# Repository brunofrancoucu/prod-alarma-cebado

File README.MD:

# Consigna
A nivel mundial, cerca de 100 millones de personas sufren de
deshidratación anualmente. Eso equivale a 3 personas por segundo!
Es nuestro deber recordar a la gente a mantenerse hidratada!

Objetivo: Hacer una alarma para tomar mate. Deben diseñar el esquemático y PCB (en KiCad), partiendo del circuito
dispuesto, y generar una bill of materials (BOM) completa.
# kicad - Esquematico y layout

Proceso de diseno placa conexiones electricas entre componentes, alineado de componentes, soldadura y manejo en gral, medición de señales, eventuales hotfixes. 
[consideraciones](/board/README.MD), [calculos](/board/README.MD#calculos), [BOM](/BOM.html)
# Autodesk Inventor - Encapsulado

Proceso de diseno del envolvente plastico
[consideraciones](/enclosure/README.md#consideraciones-housingipt)

# Producto Final

Feedback:
- Contra-peso [return force](https://www.digikey.com/en/products/detail/same-sky-formerly-cui-devices/TS02-66-90-BK-260-SCR-D/15634305) (btn push)
- USB-c
- Bateria (Conexion a placa)

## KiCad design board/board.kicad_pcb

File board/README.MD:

# Ruteo de alta frecuencia con coupling a GND Y PWR
Par diferencial de alta frecuencia por multiples capas, respetando la impedancia el return path sera por PWR (debido a stack up intermedio de GND PWR y no GND GND), por ello utilizar capacitor en puntos de entrada (source) y salida (exit) (split boundary)

### Stitching capacitor:
[ref1](https://www.asset-intertech.com/wp-content/uploads/2020/05/6a01348365b3a6970c01b8d06c22f7970c-pi.jpg), [ref2](https://www.protoexpress.com/blog/wp-content/uploads/2020/05/28.png)
Valores normales para el stitching capacitor ronda los, 10nF and 100nF [src](https://www.protoexpress.com/blog/best-high-speed-pcb-routing-practices/)
Evitar: "If that plane is cut, the return current must detour—often radiating or coupling into other nets—and you’ll get reflections, EMI, and extra crosstalk" - gpt

# Calculos:
### Par diferencial:

Z0: 90ohms +-15%
w: εᵣ 4.6 7628 prepreg FR-4 glass-epoxy laminate [ref](https://jlcpcb.com/capabilities/pcb-capabilities)
h: 0.2mm
Ancho pista: 0.202 mm - separacion pista recomendada: 0.062 mm, maxima: 0.329 mm

### Stitching capacitor, "capacitancia ideal":
Frequencia usb 3.0: 2.5 Ghz (medible con el "rise time" de la señal), entonces, para un Zdiff de 90 ohmios el Zbridge resulta 9 ohmios, capacitancia minima: 7.1 pF
- 100 nF 0402 or 0201	for low-frequency return (10 kHz – 100 MHz)	
- 1 nF 0201	covers 100 MHz – 1 GHz
- 100 pF 0201	covers 1 GHz – 3.5+ GHz (✔️ Recomendable)

Nos aseguramos: effective throughput (bit errors), calidad de señal compliance al USB.

# Complemento

### Recomendacion (plano de referencia limpio): SIG, GND, GND, (SIG + PWR)
Objetivo / desafio: mantener bajo cross talk con un coupling corto / cercano (usando PWR como plano de referencia)

### Otras alternativas:
- GND temporal en PWR (capa 3), justo arriba de par diferencial en la 4ta capa (SIG).
- Rutearlo por arriba.

# TODO
- Bateria Litio recargable
- Entrada USB-C
- Comunicacion puerto UART (notificacion escritorio)

## Gerbers
`File > Export > Fabrication Outputs > Gerbers`
1. `Generate Drill Files...` Gerber X2
2. RUN DRC...
3. Plot
4. Verificar en `Gerber View`

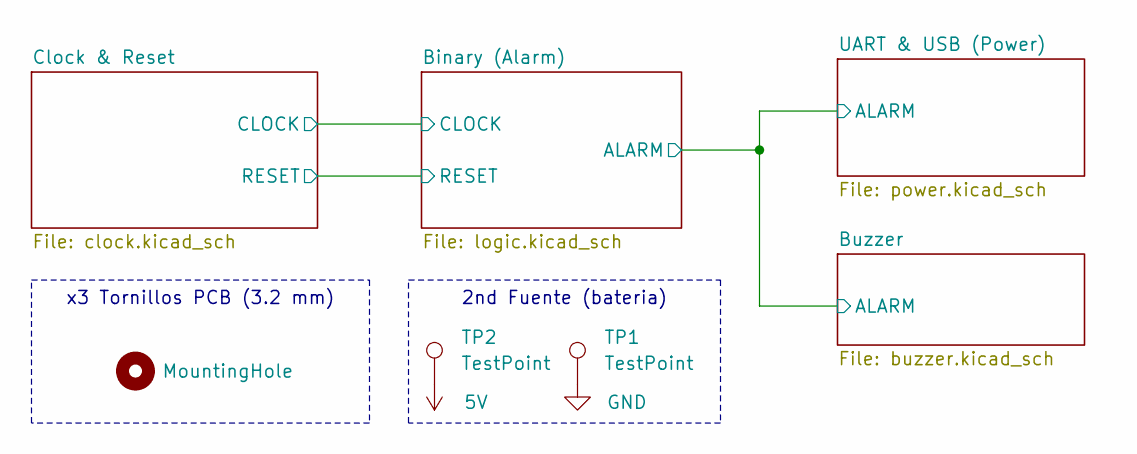
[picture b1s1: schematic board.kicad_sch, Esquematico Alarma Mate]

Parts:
H1: MountingHole; MountingHole_3.2mm_M3
TP1: TestPoint; TestPoint_THTPad_2.0x2.0mm_Drill1.0mm
TP2: TestPoint; TestPoint_THTPad_D2.0mm_Drill1.0mm

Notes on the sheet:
2nd Fuente (bateria)
x3 Tornillos PCB (3.2 mm)

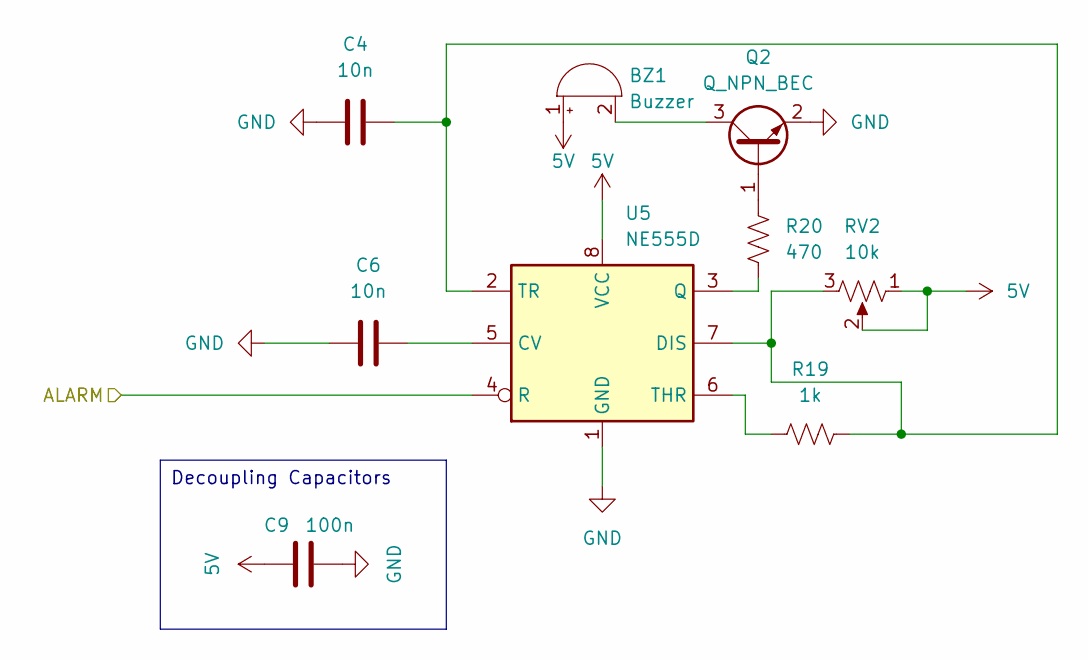
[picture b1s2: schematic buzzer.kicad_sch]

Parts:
BZ1: Buzzer; MagneticBuzzer_PUI_AT-0927-TT-6-R
C4, C6: 10n; C_0603_1608Metric
C9: 100n; C_0603_1608Metric
Q2: Q_NPN_BEC; SOT-23
R19: 1k; R_0603_1608Metric
R20: 470; R_0603_1608Metric
RV2: 10k; Potentiometer_Piher_PT-6-V_Vertical
U5: NE555D; SOIC-8_3.9x4.9mm_P1.27mm

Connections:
5V: BZ1.1 (+), C9.1, RV2.1, RV2.2, U5.8 (VCC); also elsewhere on the board
ALARM: U5.4 (R); also elsewhere on the board
GND: C4.2, C6.1, C9.2, Q2.2 (E), U5.1 (GND); also elsewhere on the board
unnamed: BZ1.2 (-), Q2.3 (C)
unnamed: Q2.1 (B), R20.1
unnamed: C6.2, U5.5 (CV)
unnamed: C4.1, R19.1, RV2.3, U5.2 (TR), U5.7 (DIS)
unnamed: R20.2, U5.3 (Q)
unnamed: R19.2, U5.6 (THR)

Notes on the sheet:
Decoupling Capacitors

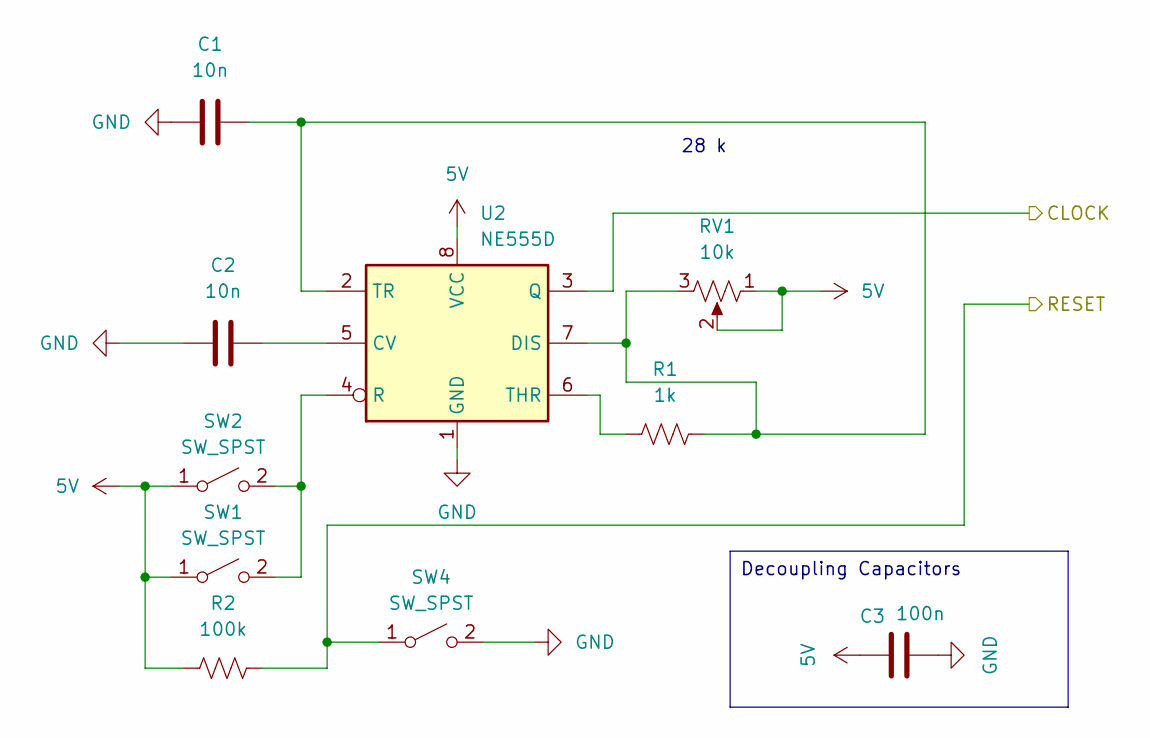
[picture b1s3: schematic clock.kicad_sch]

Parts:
C1, C2: 10n; C_0603_1608Metric
C3: 100n; C_0603_1608Metric
R1: 1k; R_0603_1608Metric
R2: 100k; R_0603_1608Metric
RV1: 10k; Potentiometer_Piher_PT-6-V_Vertical
SW1, SW2, SW4: SW_SPST; SW_PUSH_6mm_H4.3mm
U2: NE555D; SOIC-8_3.9x4.9mm_P1.27mm

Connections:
5V: C3.1, R2.1, RV1.1, RV1.2, SW1.1 (A), SW2.1 (A), U2.8 (VCC); also elsewhere on the board
CLOCK: U2.3 (Q); also elsewhere on the board
GND: C1.2, C2.1, C3.2, SW4.2 (B), U2.1 (GND); also elsewhere on the board
unnamed: SW1.2 (B), SW2.2 (B), U2.4 (R)
unnamed: C2.2, U2.5 (CV)
unnamed: C1.1, R1.1, RV1.3, U2.2 (TR), U2.7 (DIS)
unnamed: R1.2, U2.6 (THR)
RESET: R2.2, SW4.1 (A); also elsewhere on the board

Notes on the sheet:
28 k
Decoupling Capacitors

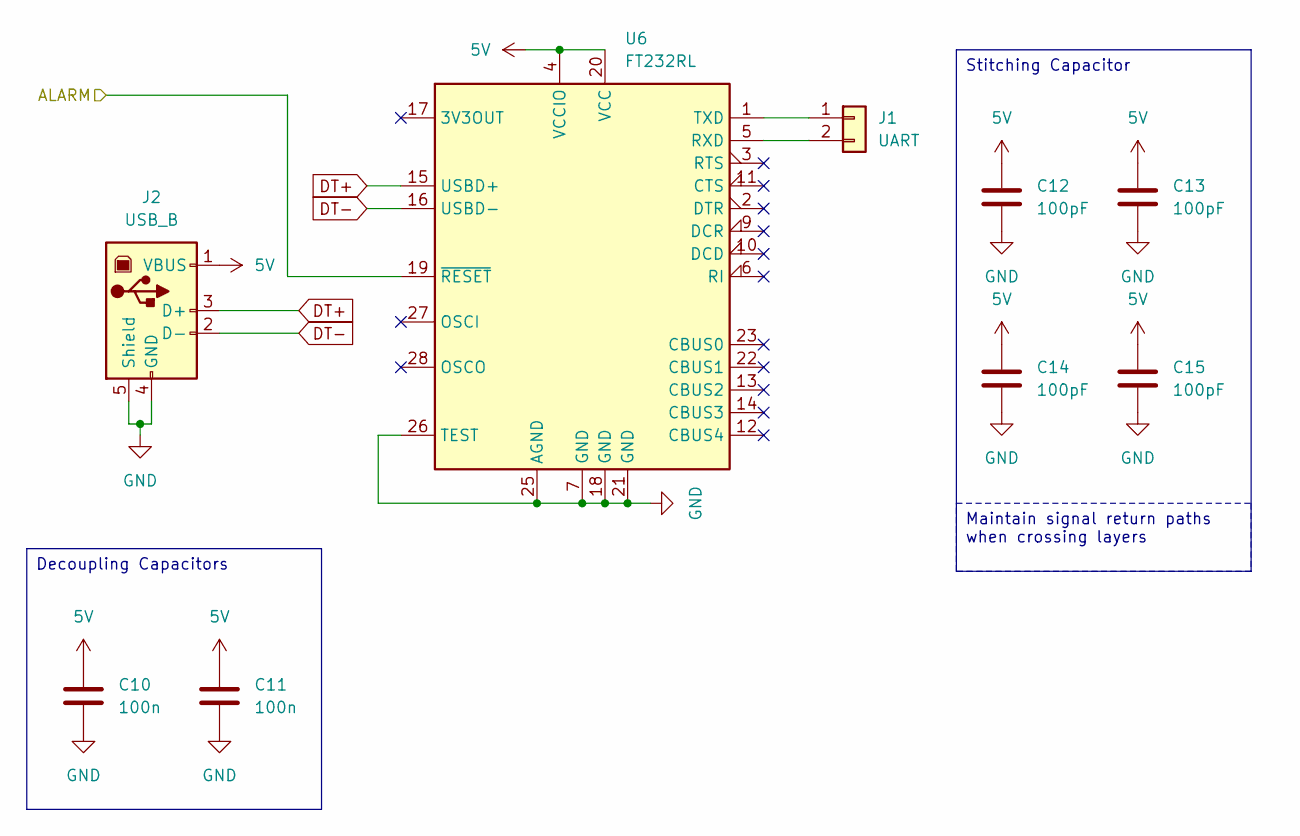
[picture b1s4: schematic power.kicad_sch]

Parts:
C10, C11: 100n; C_0603_1608Metric
C12, C13, C14, C15: 100pF; C_0201_0603Metric
J1: UART; PinSocket_1x02_P2.54mm_Vertical
J2: USB_B; USB_Mini-B_Lumberg_2486_01_Horizontal
U6: FT232RL; SSOP-28_5.3x10.2mm_P0.65mm

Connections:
5V: C10.1, C11.1, C12.1, C13.1, C14.1, C15.1, J2.1 (VBUS), U6.4 (VCCIO), U6.20 (VCC); also elsewhere on the board
ALARM: U6.19 (~RESET); also elsewhere on the board
DT+: J2.3 (D+), U6.15 (USBD+)
DT-: J2.2 (D-), U6.16 (USBD-)
GND: C10.2, C11.2, C12.2, C13.2, C14.2, C15.2, J2.4 (GND), J2.5 (Shield), U6.7 (GND), U6.18 (GND), U6.21 (GND), U6.25 (AGND), U6.26 (TEST); also elsewhere on the board
unnamed: J1.1, U6.1 (TXD)
unnamed: J1.2, U6.5 (RXD)

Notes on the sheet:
Stitching Capacitor
Maintain signal return paths when crossing layers
Decoupling Capacitors

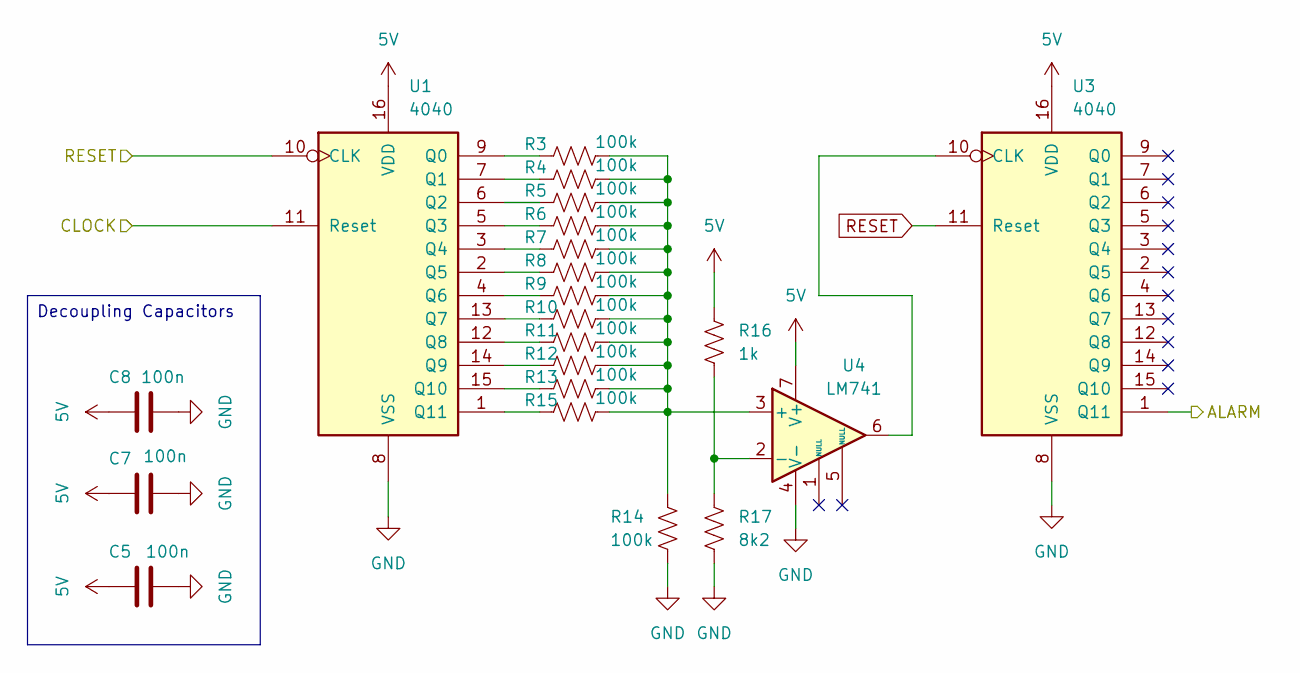
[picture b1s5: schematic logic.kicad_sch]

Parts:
C5, C7, C8: 100n; C_0603_1608Metric
R3, R4, R5, R6, R7, R8, R9, R10, R11, R12, R13, R14, R15: 100k; R_0603_1608Metric
R16: 1k; R_0603_1608Metric
R17: 8k2; R_0603_1608Metric
U1, U3: 4040; SO-16_3.9x9.9mm_P1.27mm
U4: LM741; SOIC-8_3.9x4.9mm_P1.27mm

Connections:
5V: C5.1, C7.1, C8.1, R16.2, U1.16 (VDD), U3.16 (VDD), U4.7 (V+); also elsewhere on the board
ALARM: U3.1 (Q11); also elsewhere on the board
CLOCK: U1.10 (CLK); also elsewhere on the board
GND: C5.2, C7.2, C8.2, R14.1, R17.1, U1.8 (VSS), U3.8 (VSS), U4.4 (V-); also elsewhere on the board
unnamed: R3.1, U1.9 (Q0)
unnamed: R4.1, U1.7 (Q1)
unnamed: R5.1, U1.6 (Q2)
unnamed: R6.1, U1.5 (Q3)
unnamed: R7.1, U1.3 (Q4)
unnamed: R8.1, U1.2 (Q5)
unnamed: R9.1, U1.4 (Q6)
unnamed: R10.1, U1.13 (Q7)
unnamed: R11.1, U1.12 (Q8)
unnamed: R12.1, U1.14 (Q9)
unnamed: R13.1, U1.15 (Q10)
unnamed: R15.1, U1.1 (Q11)
unnamed: U3.10 (CLK), U4.6
unnamed: R3.2, R4.2, R5.2, R6.2, R7.2, R8.2, R9.2, R10.2, R11.2, R12.2, R13.2, R14.2, R15.2, U4.3 (+)
unnamed: R16.1, R17.2, U4.2 (-)
RESET: U1.11 (Reset), U3.11 (Reset); also elsewhere on the board

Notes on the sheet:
Decoupling Capacitors

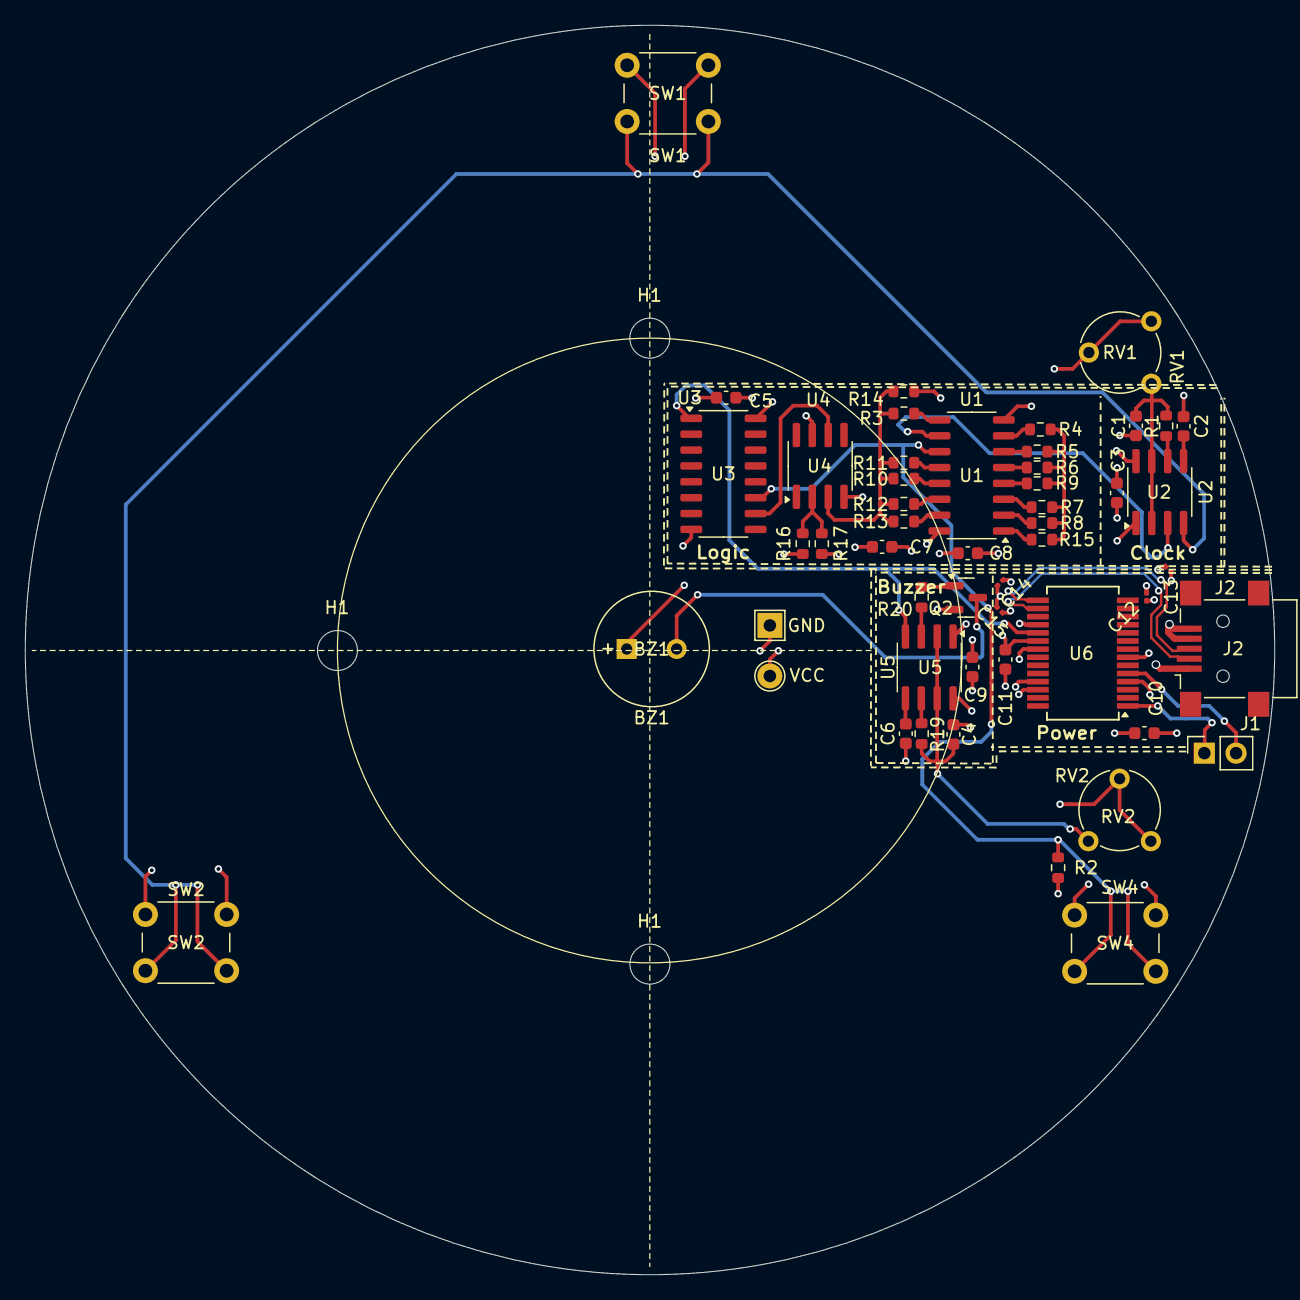
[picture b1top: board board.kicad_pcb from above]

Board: 4 copper layers, 100.0 x 100.0 mm, 54 parts (0 on the bottom side), 34 nets.

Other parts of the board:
GND: TestPoint; TestPoint_THTPad_2.0x2.0mm_Drill1.0mm
H1#2, H1#3: MountingHole; MountingHole_3.2mm_M3
VCC: TestPoint; TestPoint_THTPad_D2.0mm_Drill1.0mm

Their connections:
5V: VCC.1; also elsewhere on the board
GND: GND.1; also elsewhere on the board

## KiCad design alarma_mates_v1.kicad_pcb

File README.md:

# alarma-mates-pcb
Esquemático y diseño de PCB en KiCad de una alarma para tomar mates cada 5 minutos.

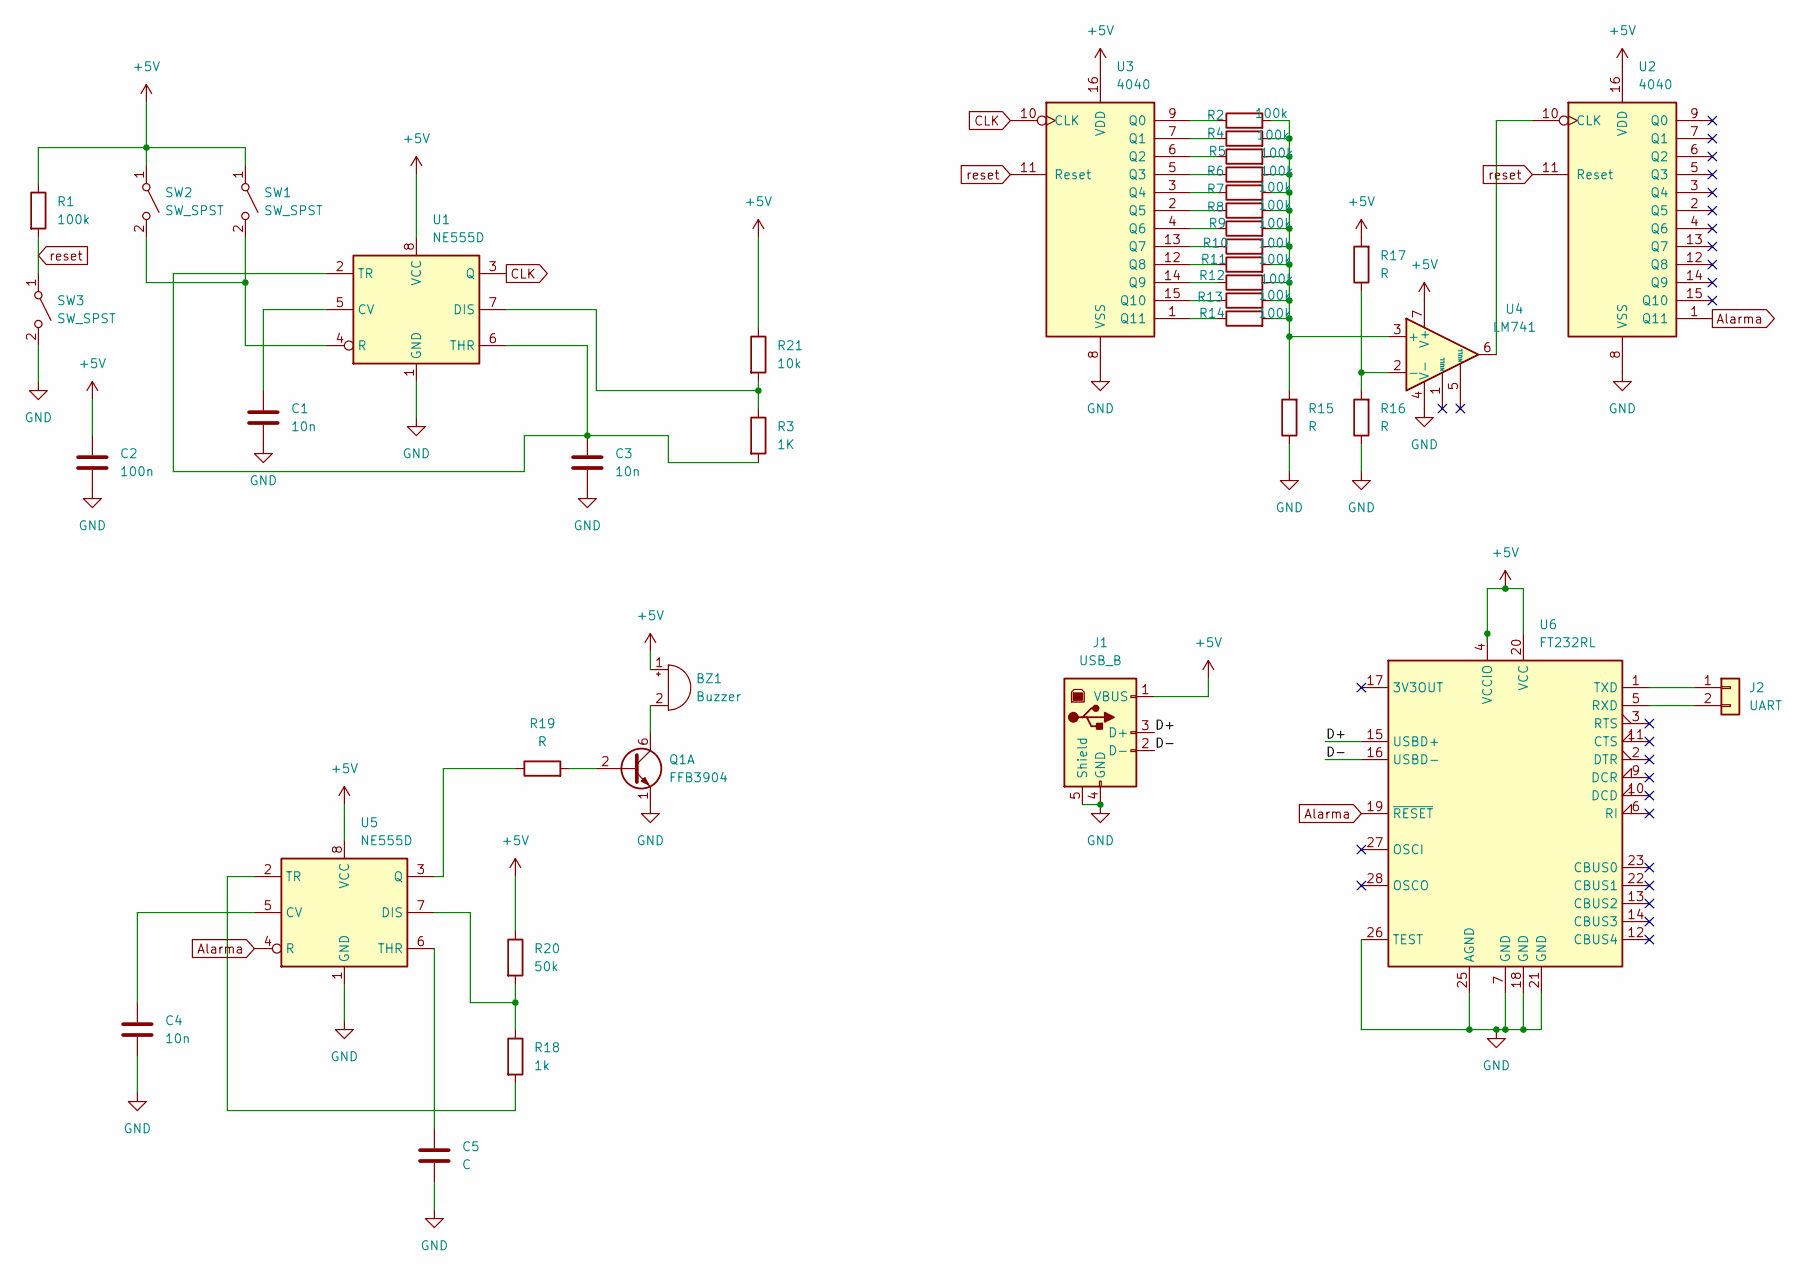
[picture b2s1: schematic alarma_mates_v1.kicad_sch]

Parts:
BZ1: Buzzer; TO_0601A_SOB
C1, C3, C4: 10n; C_0603_1608Metric
C2: 100n; C_0603_1608Metric
C5: C; C_0603_1608Metric
J1: USB_B; CUI_UJ2-MBH-1-SMT
J2: UART; PinHeader_1x02_P1.00mm_Vertical_SMD_Pin1Left
Q1: FFB3904; SOT-23_MCC
R1, R2, R4, R5, R6, R7, R8, R9, R10, R11, R12, R13, R14: 100k; R_0603_1608Metric
R3: 1K; R_0603_1608Metric
R15, R16, R17, R19: R; R_0603_1608Metric
R18: 1k; R_0603_1608Metric
R20: 50k; R_0603_1608Metric
R21: 10k; R_0603_1608Metric
SW1, SW2, SW3: SW_SPST; SW_TS02-66-90-BK-260-SCR-D
U1, U5: NE555D; D8
U2, U3: 4040; SOT109-1_NXP
U4: LM741; D8
U6: FT232RL; SSOP-28_FTD

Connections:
+5V: BZ1.1 (+), C2.1, J1.1 (VBUS), R1.1, R17.2, R20.1, R21.1, SW1.1 (A), SW2.1 (A), U1.8 (VCC), U2.16 (VDD), U3.16 (VDD), U4.7 (V+), U5.8 (VCC), U6.4 (VCCIO), U6.20 (VCC)
/D+: J1.3 (D+), U6.15 (USBD+)
/D-: J1.2 (D-), U6.16 (USBD-)
Alarma: U2.1 (Q11), U5.4 (R), U6.19 (~RESET)
CLK: U1.3 (Q), U3.10 (CLK)
GND: C1.2, C2.2, C3.2, C4.2, C5.2, J1.4 (GND), J1.5 (Shield), Q1.1 (E1), R15.1, R16.1, SW3.2 (B), U1.1 (GND), U2.8 (VSS), U3.8 (VSS), U4.4 (V-), U5.1 (GND), U6.7 (GND), U6.18 (GND), U6.21 (GND), U6.25 (AGND), U6.26 (TEST)
unnamed: BZ1.2 (-), Q1.6 (C1)
unnamed: J2.1, U6.1 (TXD)
unnamed: J2.2, U6.5 (RXD)
unnamed: Q1.2 (B1), R19.2
unnamed: SW1.2 (B), SW2.2 (B), U1.4 (R)
unnamed: C1.1, U1.5 (CV)
unnamed: R3.1, R21.2, U1.7 (DIS)
unnamed: C3.1, R3.2, U1.2 (TR), U1.6 (THR)
unnamed: U2.10 (CLK), U4.6
unnamed: R2.1, U3.9 (Q0)
unnamed: R4.1, U3.7 (Q1)
unnamed: R5.1, U3.6 (Q2)
unnamed: R6.1, U3.5 (Q3)
unnamed: R7.1, U3.3 (Q4)
unnamed: R8.1, U3.2 (Q5)
unnamed: R9.1, U3.4 (Q6)
unnamed: R10.1, U3.13 (Q7)
unnamed: R11.1, U3.12 (Q8)
unnamed: R12.1, U3.14 (Q9)
unnamed: R13.1, U3.15 (Q10)
unnamed: R14.1, U3.1 (Q11)
unnamed: R2.2, R4.2, R5.2, R6.2, R7.2, R8.2, R9.2, R10.2, R11.2, R12.2, R13.2, R14.2, R15.2, U4.3 (+)
unnamed: R16.2, R17.1, U4.2 (-)
unnamed: C4.1, U5.5 (CV)
unnamed: R18.1, R20.2, U5.7 (DIS)
unnamed: R19.1, U5.3 (Q)
unnamed: C5.1, U5.6 (THR)
unnamed: R18.2, U5.2 (TR)
reset: R1.2, SW3.1 (A), U2.11 (Reset), U3.11 (Reset)

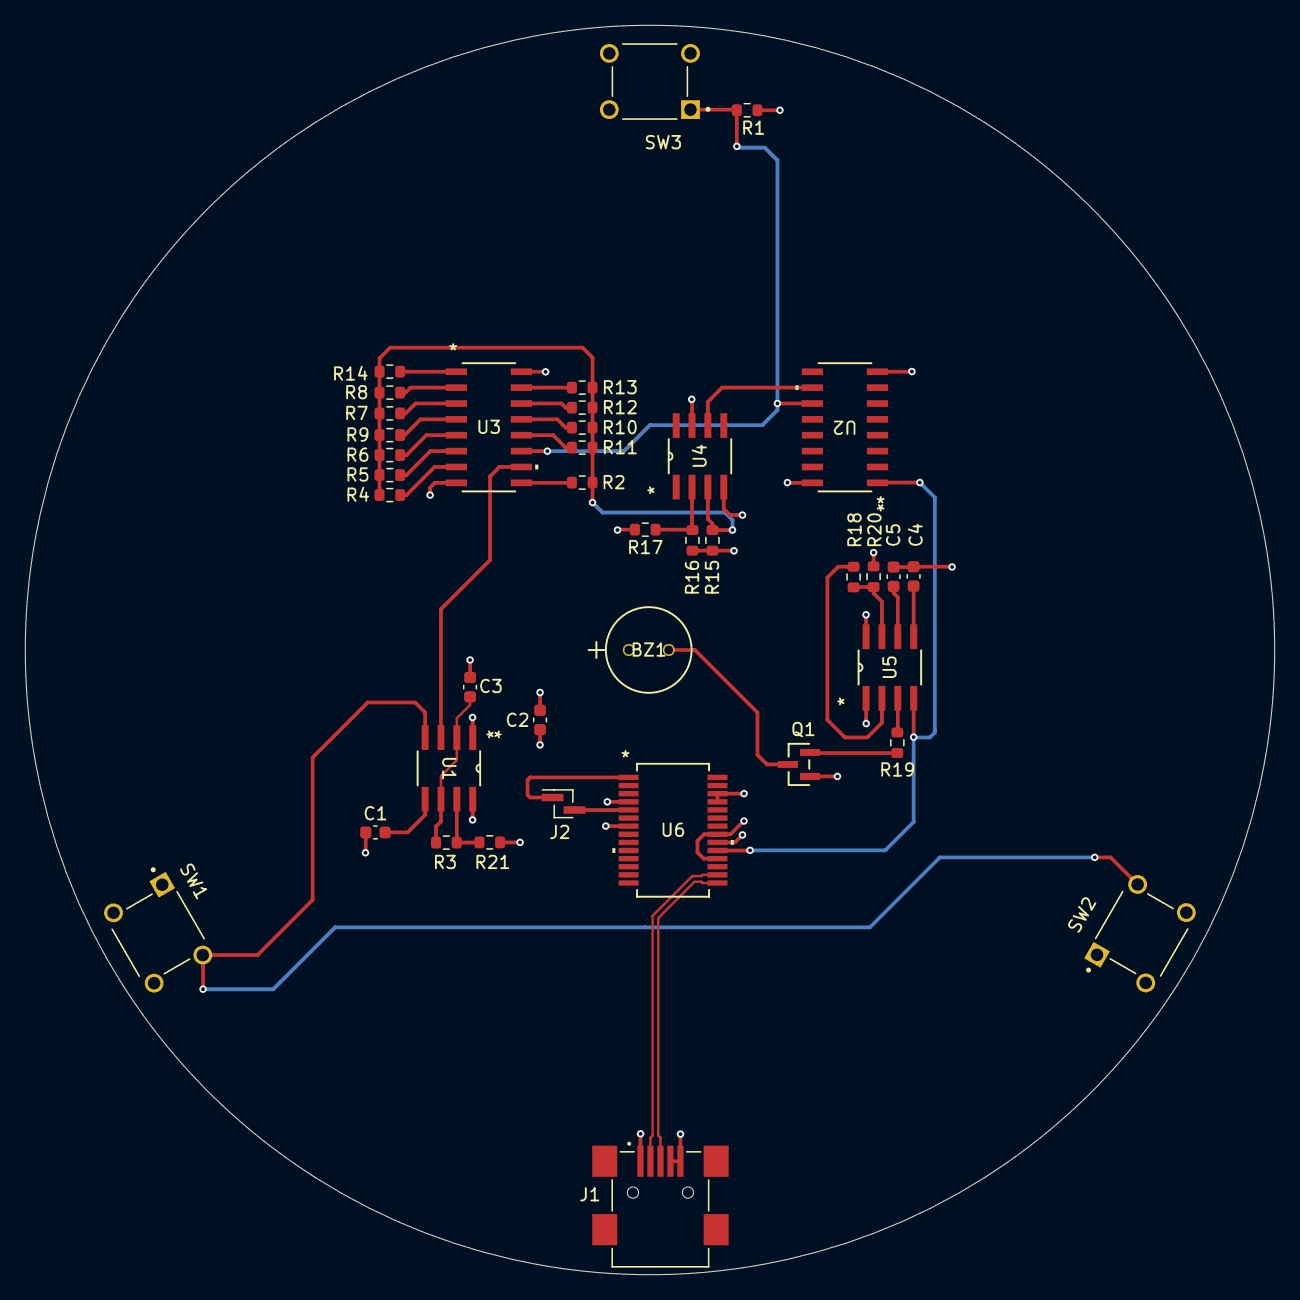
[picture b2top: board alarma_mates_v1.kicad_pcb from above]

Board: 4 copper layers, 100.0 x 100.0 mm, 39 parts (0 on the bottom side), 35 nets.

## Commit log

2025-07-13 doc: add TODO
2025-07-23 add: ignore
2025-07-23 chore: exclude backups
2025-07-23 chore: prefix bad
2025-07-23 chore
2025-07-23 refactor: moved to board
2025-07-23 add: layout, gerbers
2025-07-23 refactor: renamed
2025-07-23 chore: fx
2025-07-23 add: missing files
2025-07-23 add: ignr
2025-07-23 add: vias through - fix: routes
2025-07-23 add: stitching capacitor & gerbers
2025-07-27 add: Hierarchical Sheets
2025-07-27 chore: save, backup files
2025-07-27 add: Mounting holes, box comments
2025-07-27 add: net class directive
2025-07-27 add: pcb layout & gerbers
2025-07-28 add: Theme
2025-07-28 add: Referencias en Silkscreen centradas al componente
2025-07-28 add: 3 mechanical holes & .step 3d
2025-07-28 typo
2025-07-29 add: product enclosure
2025-07-30 add: 9mm 3d push btn, VCC GND pins (battery)
2025-07-30 add: rectangle TIP GNS
2025-07-30 add: hosuing & plate (latest)
2025-07-30 doc: CAD
2025-07-30 add: sch darkmode
2025-07-30 doc: add concepcion
2025-07-30 doc: main
2025-07-30 add: cover motion constrain
